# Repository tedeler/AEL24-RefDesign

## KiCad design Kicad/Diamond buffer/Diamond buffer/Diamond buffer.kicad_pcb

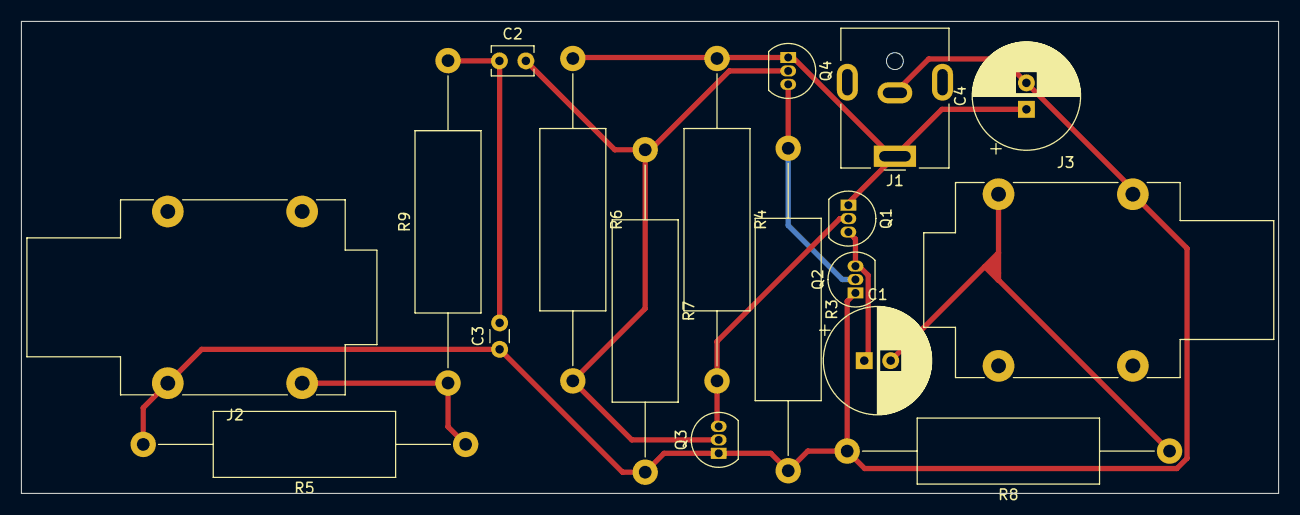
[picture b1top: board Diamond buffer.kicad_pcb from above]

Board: 2 copper layers, 118.9 x 44.6 mm, 18 parts (0 on the bottom side), 9 nets.

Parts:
C1, C4: 100u; CP_Radial_D10.0mm_P2.50mm
C2: 100n; C_Disc_D3.8mm_W2.6mm_P2.50mm
C3: 2n2; C_Disc_D3.0mm_W1.6mm_P2.50mm
J1: Jack-DC; BarrelJack_CUI_PJ-063AH_Horizontal
J2, J3: AudioJack2_Ground; Jack_6.35mm_Neutrik_NMJ4HFD2_Horizontal
Q1, Q4: BC550; TO-92_Inline
Q2, Q3: BC560; TO-92_Inline
R3, R4: 2k; R_Axial_DIN0617_L17.0mm_D6.0mm_P30.48mm_Horizontal
R5, R6, R7, R8: 2 MEG; R_Axial_DIN0617_L17.0mm_D6.0mm_P30.48mm_Horizontal
R9: 47; R_Axial_DIN0617_L17.0mm_D6.0mm_P30.48mm_Horizontal

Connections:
unnamed: C1.2, J3.T, R8.1
unnamed: C2.1, C3.2, R9.2
unnamed: J2.T, R5.1, R9.1
unnamed: Q1.2 (B), Q3.3 (E), R4.2
unnamed: C4.1, J1.1, Q1.1 (C), Q4.1 (C), R4.1, R6.1
unnamed: C1.1, Q1.3 (E), Q2.3 (E)
unnamed: Q2.2 (B), Q4.3 (E), R3.1
unnamed: C3.1, C4.2, J1.2, J2.S, J3.S, Q2.1 (C), Q3.1 (C), R3.2, R5.2, R7.2, R8.2
unnamed: C2.2, Q3.2 (B), Q4.2 (B), R6.2, R7.1

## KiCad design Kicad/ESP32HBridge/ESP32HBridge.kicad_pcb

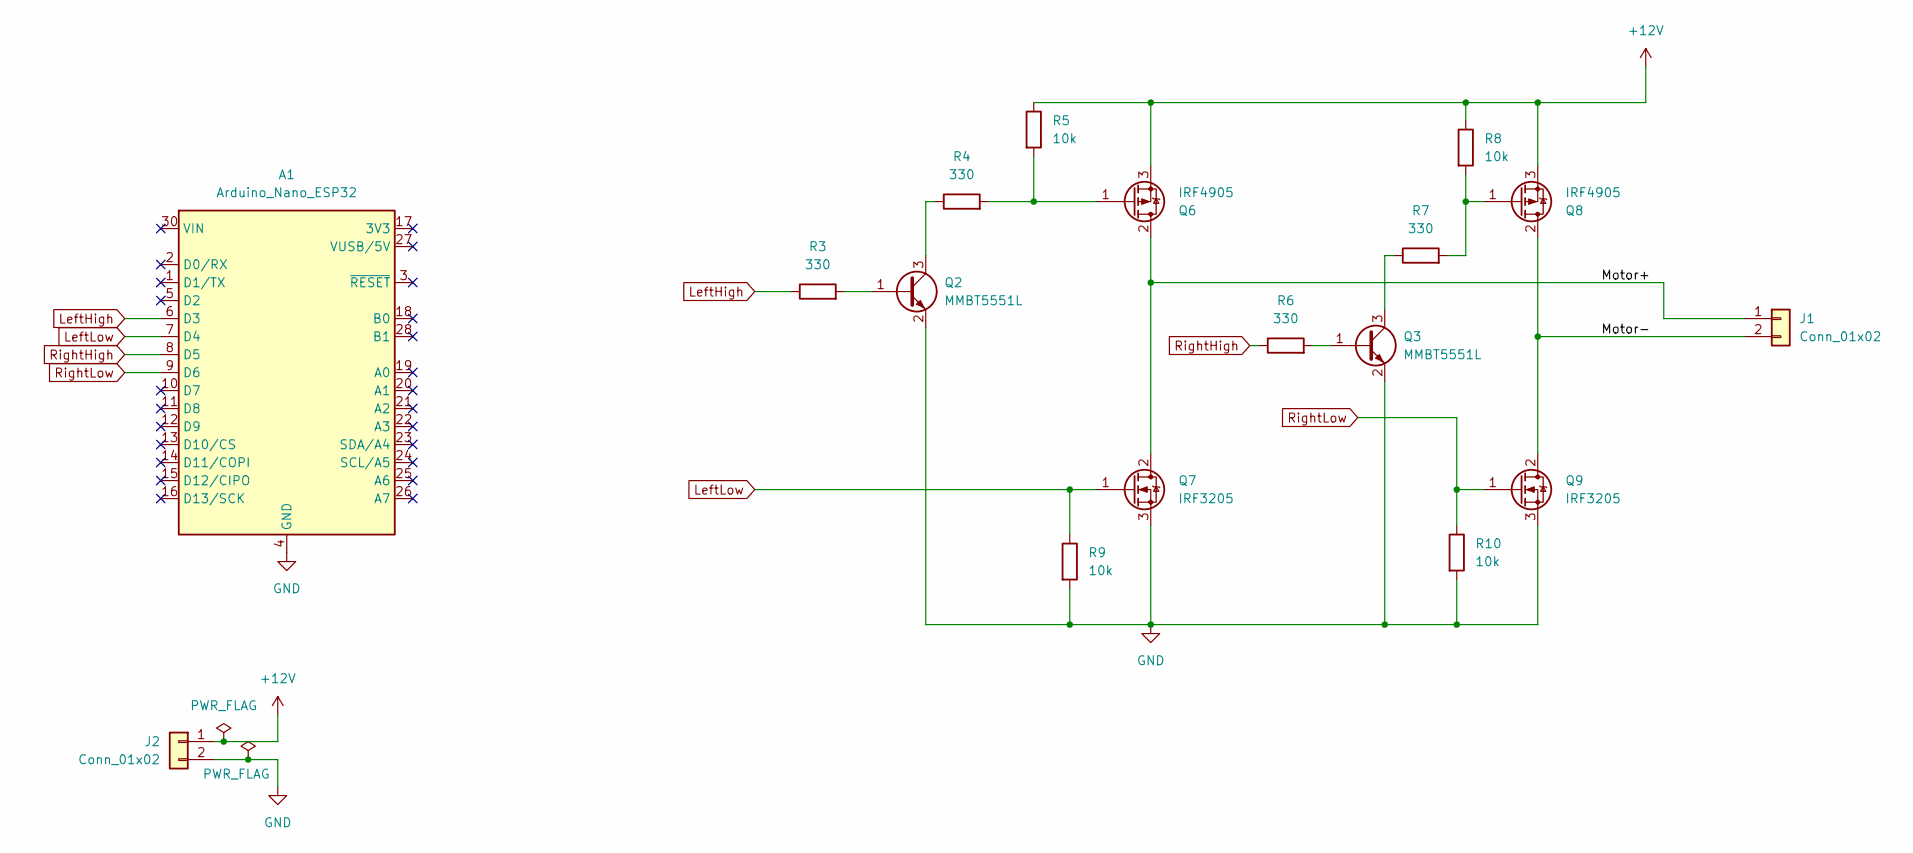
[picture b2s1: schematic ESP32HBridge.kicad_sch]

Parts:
A1: Arduino_Nano_ESP32; Arduino_Nano
J1: Conn_01x02; TE_440055-2_1x02_P2.00mm_Horizontal
J2: Conn_01x02; PhoenixContact_MCV_1,5_2-G-3.5_1x02_P3.50mm_Vertical
Q2, Q3: MMBT5551L; SOT-23; MPN C2145
Q6, Q8: IRF4905; TO-220-3_Vertical
Q7, Q9: IRF3205; TO-220-3_Vertical
R3, R4, R6, R7: 330; R_0805_2012Metric; MPN C17630
R5, R8, R9, R10: 10k; R_0805_2012Metric; MPN C17414

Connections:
+12V: J2.1, Q6.3 (S), Q8.3 (S), R5.1, R8.1
/Motor+: J1.1, Q6.2 (D), Q7.2 (D)
/Motor-: J1.2, Q8.2 (D), Q9.2 (D)
GND: A1.4 (GND), A1.29 (GND), J2.2, Q2.2 (E), Q3.2 (E), Q7.3 (S), Q9.3 (S), R9.2, R10.2
LeftHigh: A1.6 (D3), R3.1
LeftLow: A1.7 (D4), Q7.1 (G), R9.1
unnamed: Q2.1 (B), R3.2
unnamed: Q2.3 (C), R4.1
unnamed: Q3.1 (B), R6.2
unnamed: Q3.3 (C), R7.1
unnamed: Q6.1 (G), R4.2, R5.2
unnamed: Q8.1 (G), R7.2, R8.2
RightHigh: A1.8 (D5), R6.1
RightLow: A1.9 (D6), Q9.1 (G), R10.1

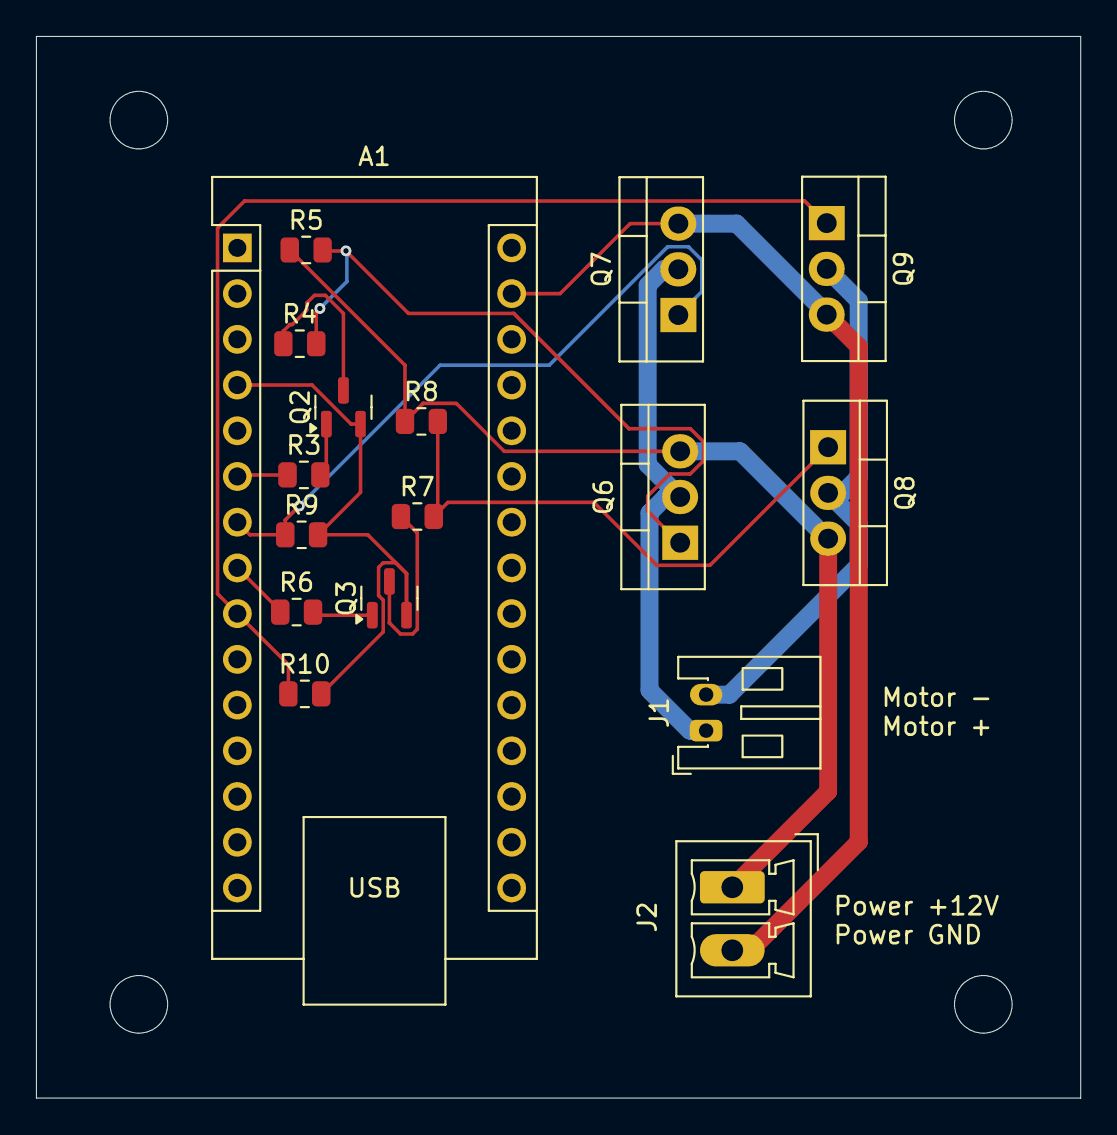
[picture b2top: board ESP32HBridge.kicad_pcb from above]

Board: 2 copper layers, 58.0 x 59.0 mm, 17 parts (0 on the bottom side), 14 nets.

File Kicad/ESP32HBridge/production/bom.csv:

Designator,Footprint,Quantity,Value,LCSC Part #
A1,Arduino_Nano,1,Arduino_Nano_ESP32,
J1,TE_440055-2_1x02_P2.00mm_Horizontal,1,Conn_01x02,
J2,"PhoenixContact_MCV_1,5_2-G-3.5_1x02_P3.50mm_Vertical",1,Conn_01x02,
"Q2, Q3",SOT-23,2,MMBT5551L,C2145
"Q6, Q8",TO-220-3_Vertical,2,IRF4905,
"Q7, Q9",TO-220-3_Vertical,2,IRF3205,
"R10, R5, R8, R9",0805,4,10k,C17414
"R3, R4, R6, R7",0805,4,330,C17630

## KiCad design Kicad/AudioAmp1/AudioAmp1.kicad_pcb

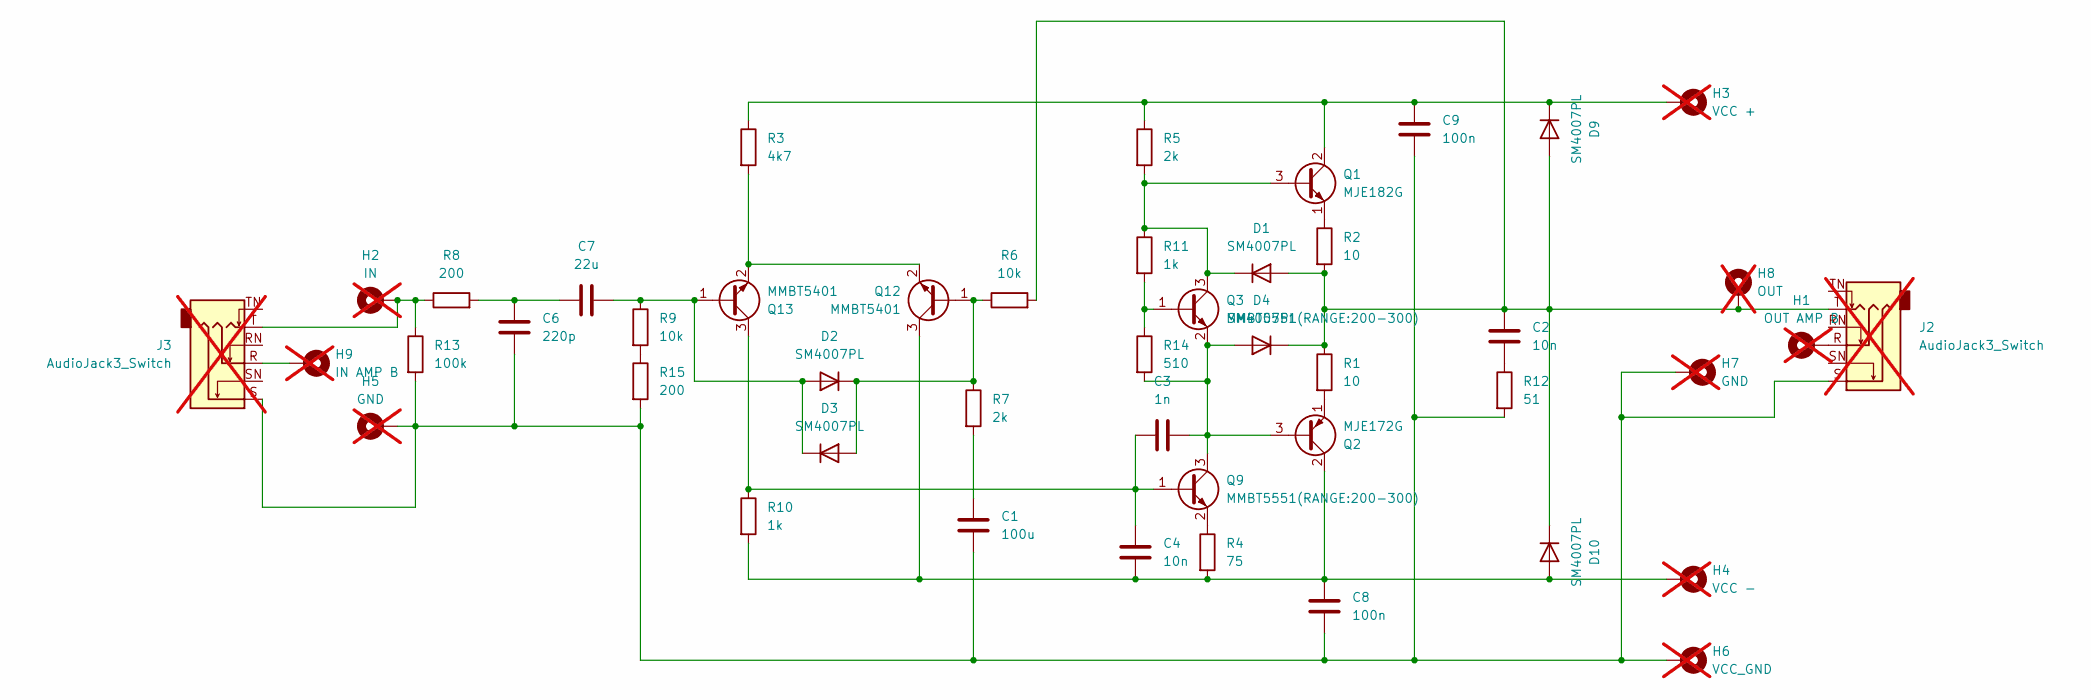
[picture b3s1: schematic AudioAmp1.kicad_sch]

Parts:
C1: 100u; C_1206_3216Metric; MPN C15008
C2, C4: 10n; C_0805_2012Metric; MPN C1710
C3: 1n; C_0603_1608Metric; MPN C1588
C6: 220p; C_0603_1608Metric; MPN C1603
C7: 22u; C_1206_3216Metric; MPN C12891
C8, C9: 100n; C_0603_1608Metric; MPN C14663
D1, D2, D3, D4, D9, D10: SM4007PL; D_SOD-123F; MPN C64898
H1: OUT AMP B; MountingHole_2.5mm_Pad; not fitted
H2: IN; MountingHole_2.5mm_Pad; not fitted
H3: VCC +; MountingHole_2.5mm_Pad; not fitted
H4: VCC -; MountingHole_2.5mm_Pad; not fitted
H5, H7: GND; MountingHole_2.5mm_Pad; not fitted
H6: VCC_GND; MountingHole_2.5mm_Pad; not fitted
H8: OUT; MountingHole_2.5mm_Pad; not fitted
H9: IN AMP B; MountingHole_2.5mm_Pad; not fitted
J2, J3: AudioJack3_Switch; Jack_6.35mm_Neutrik_NMJ6HCD2_Horizontal; not fitted
Q1: MJE182G; TO229P800X325X1420-3; MPN C27681
Q2: MJE172G; TO229P800X325X1420-3; MPN C27682
Q3, Q9: MMBT5551(RANGE:200-300); SOT-23
Q12, Q13: MMBT5401; SOT-23; MPN C8326
R1, R2: 10; R_1206_3216Metric; MPN C17903
R3: 4k7; R_1206_3216Metric; MPN C17936
R4: 75; R_0603_1608Metric; MPN C4275
R5, R7: 2k; R_1206_3216Metric; MPN C17944
R6, R9: 10k; R_1206_3216Metric; MPN C17902
R8, R15: 200; R_0805_2012Metric; MPN C17540
R10, R11: 1k; R_1206_3216Metric; MPN C4410
R12: 51; R_0805_2012Metric; MPN C17738
R13: 100k; R_1206_3216Metric; MPN C17900
R14: 510; R_0805_2012Metric_Pad1.20x1.40mm_HandSolder; MPN C17734

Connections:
unnamed: C1.1, R7.2
unnamed: C1.2, C6.2, C8.2, C9.2, H5.1, H6.1, H7.1, J2.S, J3.S, R12.2, R13.2, R15.2
unnamed: C2.2, R12.1
unnamed: C6.1, C7.1, R8.2
unnamed: C2.1, D1.2 (A), D4.1 (K), D9.2 (A), D10.1 (K), H8.1, J2.T, R1.1, R2.2, R6.2
unnamed: D1.1 (K), Q1.3 (B), Q3.3 (C), R5.2, R11.1
unnamed: C7.2, D2.2 (A), D3.1 (K), Q13.1 (B), R9.1
unnamed: D2.1 (K), D3.2 (A), Q12.1 (B), R6.1, R7.1
unnamed: C3.2, D4.2 (A), Q2.3 (B), Q3.2 (E), Q9.3 (C), R14.2
unnamed: C9.1, D9.1 (K), H3.1, Q1.2 (C), R3.1, R5.1
unnamed: C4.2, C8.1, D10.2 (A), H4.1, Q2.2 (C), Q12.3 (C), R4.2, R10.2
unnamed: H1.1, J2.R
unnamed: H2.1, J3.T, R8.1, R13.1
unnamed: H9.1, J3.R
unnamed: Q1.1 (E), R2.1
unnamed: Q2.1 (E), R1.2
unnamed: Q3.1 (B), R11.2, R14.1
unnamed: Q9.2 (E), R4.1
unnamed: Q12.2 (E), Q13.2 (E), R3.2
unnamed: C3.1, C4.1, Q9.1 (B), Q13.3 (C), R10.1
unnamed: R9.2, R15.1

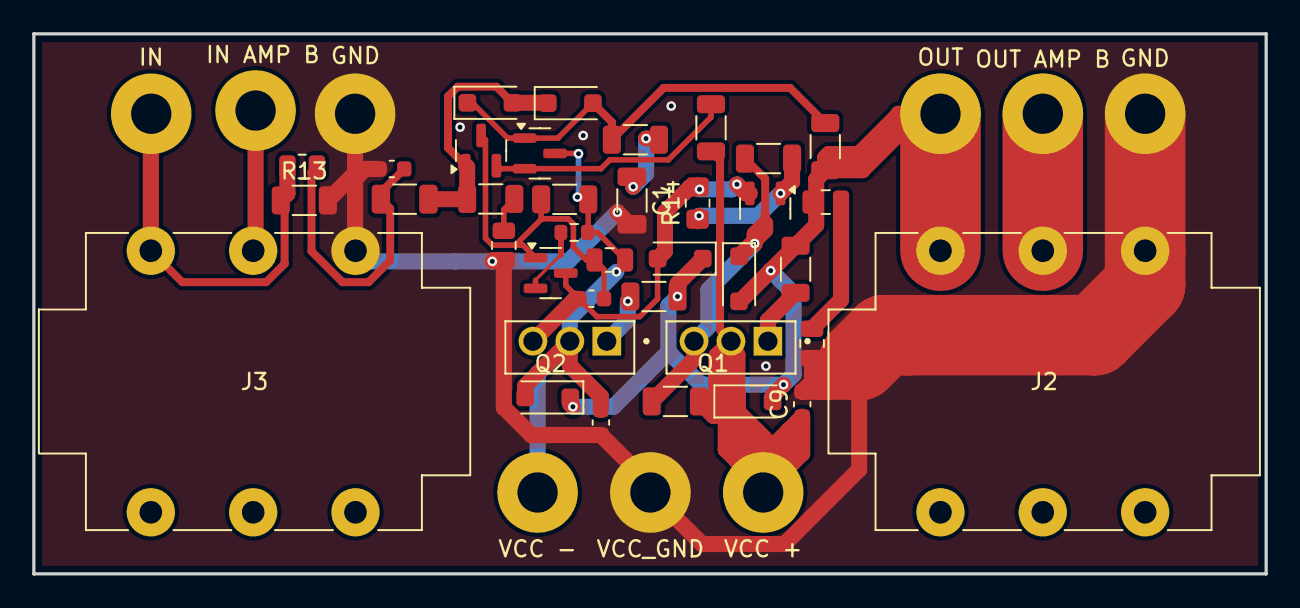
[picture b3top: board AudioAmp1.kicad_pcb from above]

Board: 2 copper layers, 76.5 x 33.5 mm, 46 parts (0 on the bottom side), 21 nets.

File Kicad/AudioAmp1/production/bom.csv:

Designator,Footprint,Quantity,Value,LCSC Part #
C1,1206,1,100u,C15008
"C2, C4",0805,2,10n,C1710
C3,0603,1,1n,C1588
C6,0603,1,220p,C1603
C7,1206,1,22u,C12891
"C8, C9",0603,2,100n,C14663
"D1, D10, D2, D3, D4, D9",D_SOD-123F,6,SM4007PL,C64898
Q1,TO229P800X325X1420-3,1,MJE182G,C27681
"Q12, Q13",SOT-23,2,MMBT5401,C8326
Q2,TO229P800X325X1420-3,1,MJE172G,C27682
"Q3, Q9",SOT-23,2,MMBT5551(RANGE:200-300),
"R1, R2",1206,2,10,C17903
"R10, R11",1206,2,1k,C4410
R12,0805,1,51,C17738
R13,1206,1,100k,C17900
R14,0805,1,510,C17734
"R15, R8",0805,2,200,C17540
R3,1206,1,4k7,C17936
R4,0603,1,75,C4275
"R5, R7",1206,2,2k,C17944
"R6, R9",1206,2,10k,C17902

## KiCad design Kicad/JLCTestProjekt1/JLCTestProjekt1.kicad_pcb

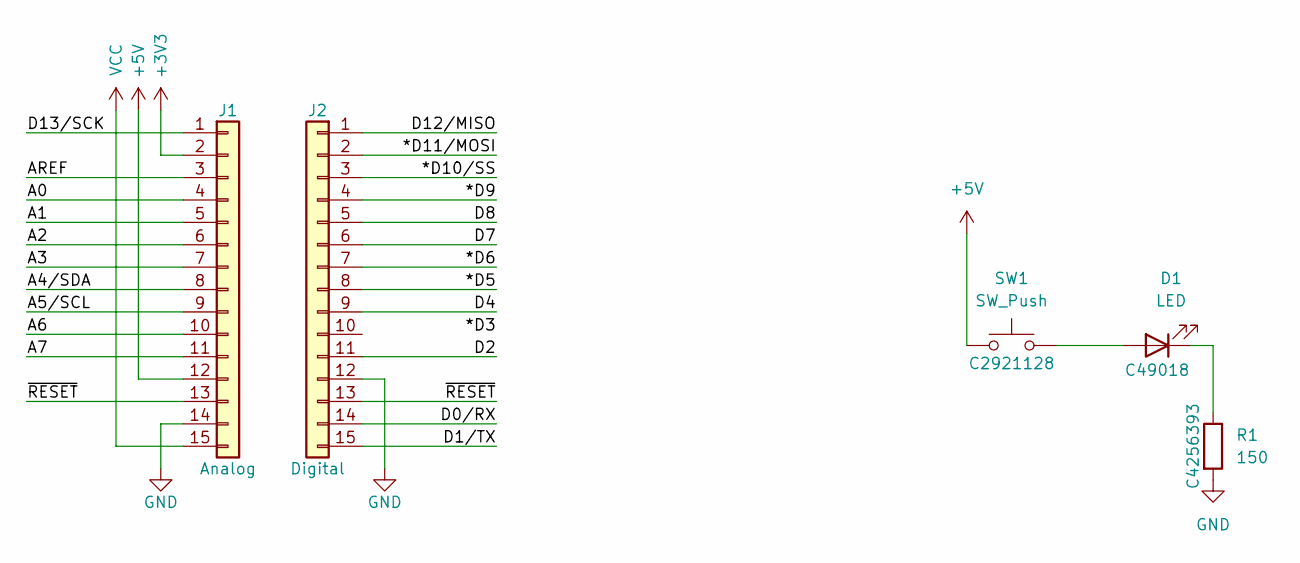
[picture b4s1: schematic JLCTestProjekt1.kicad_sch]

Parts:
D1: LED; LED_1206_3216Metric; MPN C49018
J1: Analog; PinHeader_1x15_P2.54mm_Vertical
J2: Digital; PinHeader_1x15_P2.54mm_Vertical
R1: 150; R_0805_2012Metric; MPN C4256393
SW1: SW_Push; SW_Push_1P1T_XKB_TS-1187A; MPN C2921128

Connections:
+3V3: J1.2
+5V: J1.12, SW1.1
/*D5: J2.8
/*D6: J2.7
/*D9: J2.4
/*D10/SS: J2.3
/*D11/MOSI: J2.2
/A0: J1.4
/A1: J1.5
/A2: J1.6
/A3: J1.7
/A4/SDA: J1.8
/A5/SCL: J1.9
/A6: J1.10
/A7: J1.11
/AREF: J1.3
/D0/RX: J2.14
/D1/TX: J2.15
/D2: J2.11
/D4: J2.9
/D7: J2.6
/D8: J2.5
/D12/MISO: J2.1
/D13/SCK: J1.1
/~RESET: J1.13, J2.13
GND: J1.14, J2.12, R1.2
unnamed: D1.2 (A), SW1.2
unnamed: D1.1 (K), R1.1
VCC: J1.15

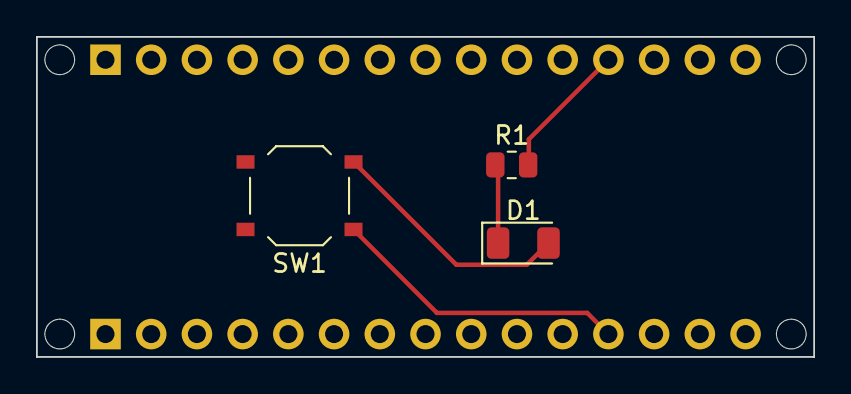
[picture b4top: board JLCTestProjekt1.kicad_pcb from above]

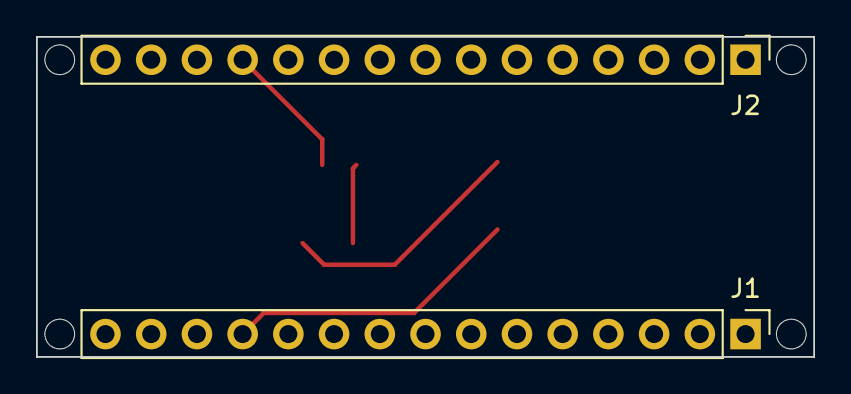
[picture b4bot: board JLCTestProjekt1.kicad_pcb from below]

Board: 2 copper layers, 43.2 x 17.8 mm, 9 parts (2 on the bottom side), 5 nets.

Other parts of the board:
MH1, MH2, MH3, MH4: MountingHole_65mil

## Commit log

2025-02-27 Initiale KiCad Projekte
2025-02-27 Änderung1
2025-02-27 Änderung 2
2025-02-27 Hab ich geändert
2025-02-27 Einmal Schaltung
2025-02-27 First Design of Test Circuit
2025-02-27 Footprint korrigiert und MPN als Eigenschaft
2025-03-04 Überarbeitetes Design auf Basis dessen was es als BasicParts bei JLC gibt
2025-03-04 Design fertig für Produktion bitte Prüfen und freigeben
2025-03-27 DemoHBridge
2025-03-27 Comit
2025-03-27 Einmal Stromverstärker
